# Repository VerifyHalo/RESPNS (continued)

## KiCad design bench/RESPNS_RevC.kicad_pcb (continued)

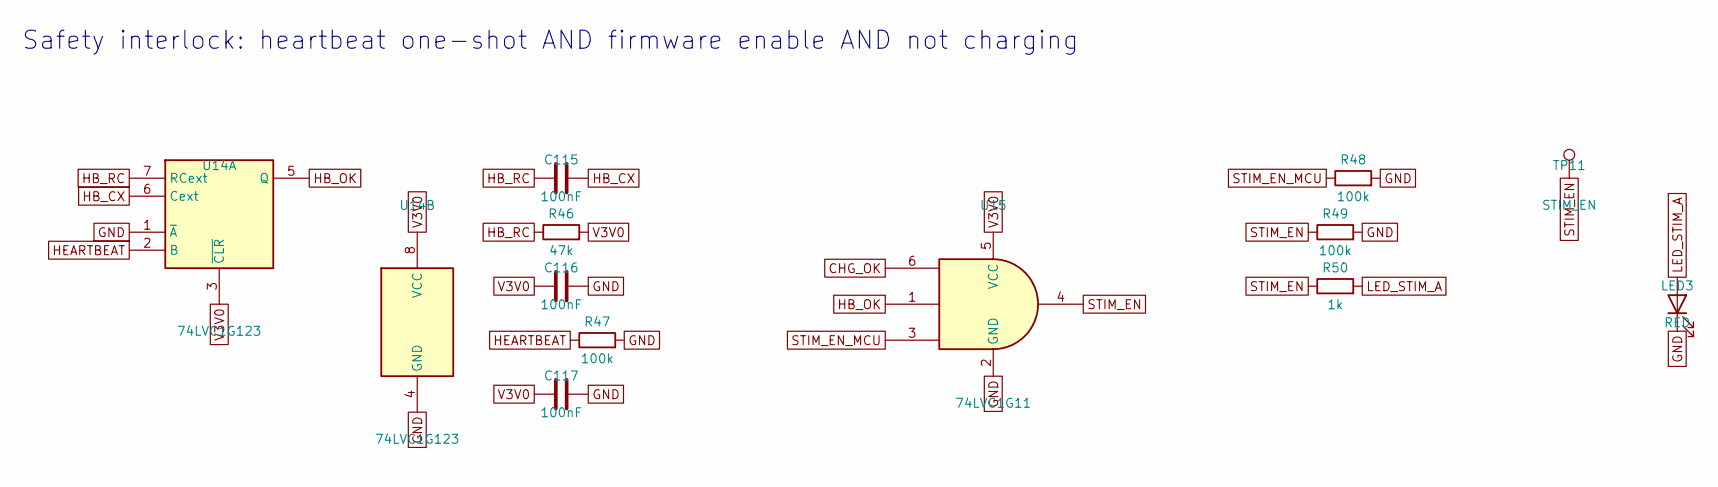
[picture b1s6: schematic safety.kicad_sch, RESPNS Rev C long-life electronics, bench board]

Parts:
C115, C116, C117: 100nF; C_0402_1005Metric; MPN CL05B104KO5NNNC
LED3: RED; LED_0603_1608Metric; MPN 19-217/R6C-AL1M2VY/6T
R46: 47k; R_0402_1005Metric; MPN 0402WGF4702TCE
R47, R48, R49: 100k; R_0402_1005Metric; MPN 0402WGF1003TCE
R50: 1k; R_0402_1005Metric; MPN 0402WGF1001TCE
TP11: STIM_EN; TestPoint_Pad_D1.0mm
U14: 74LVC1G123; VSSOP-8_2.3x2mm_P0.5mm; MPN SN74LVC1G123DCUR
U15: 74LVC1G11; SOT-363_SC-70-6; MPN SN74LVC1G11DCKR

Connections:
CHG_OK: U15.6; also elsewhere on the board
GND: C116.2, C117.2, LED3.1 (K), R47.2, R48.2, R49.2, U14.1 (~A), U14.4 (GND), U15.2 (GND); also elsewhere on the board
HB_CX: C115.2, U14.6 (Cext)
HB_OK: U14.5 (Q), U15.1
HB_RC: C115.1, R46.1, U14.7 (RCext)
HEARTBEAT: R47.1, U14.2 (B); also elsewhere on the board
LED_STIM_A: LED3.2 (A), R50.2
STIM_EN: R49.1, R50.1, TP11.1, U15.4; also elsewhere on the board
STIM_EN_MCU: R48.1, U15.3; also elsewhere on the board
V3V0: C116.1, C117.1, R46.2, U14.3 (~CLR), U14.8 (VCC), U15.5 (VCC); also elsewhere on the board

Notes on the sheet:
Safety interlock: heartbeat one-shot AND firmware enable AND not charging

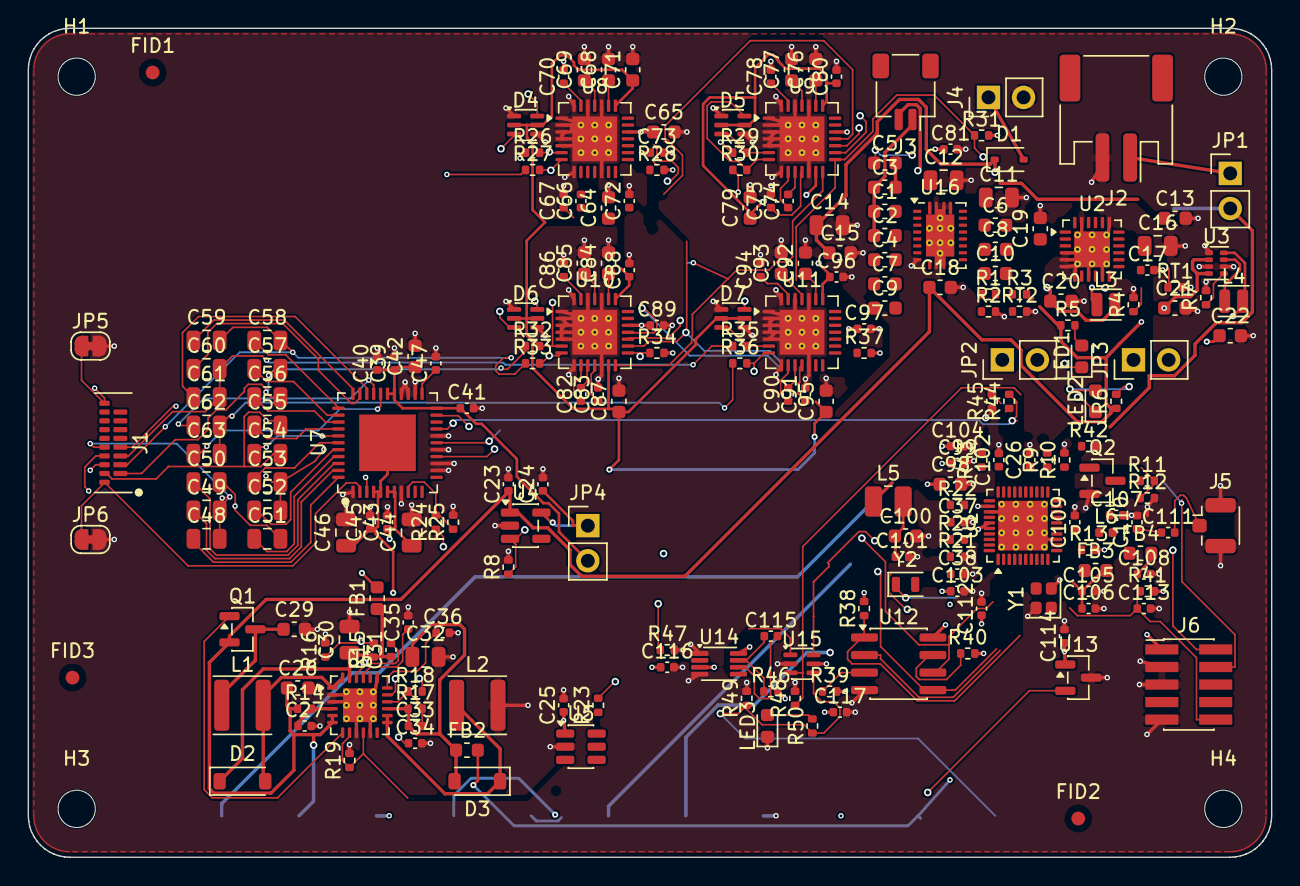
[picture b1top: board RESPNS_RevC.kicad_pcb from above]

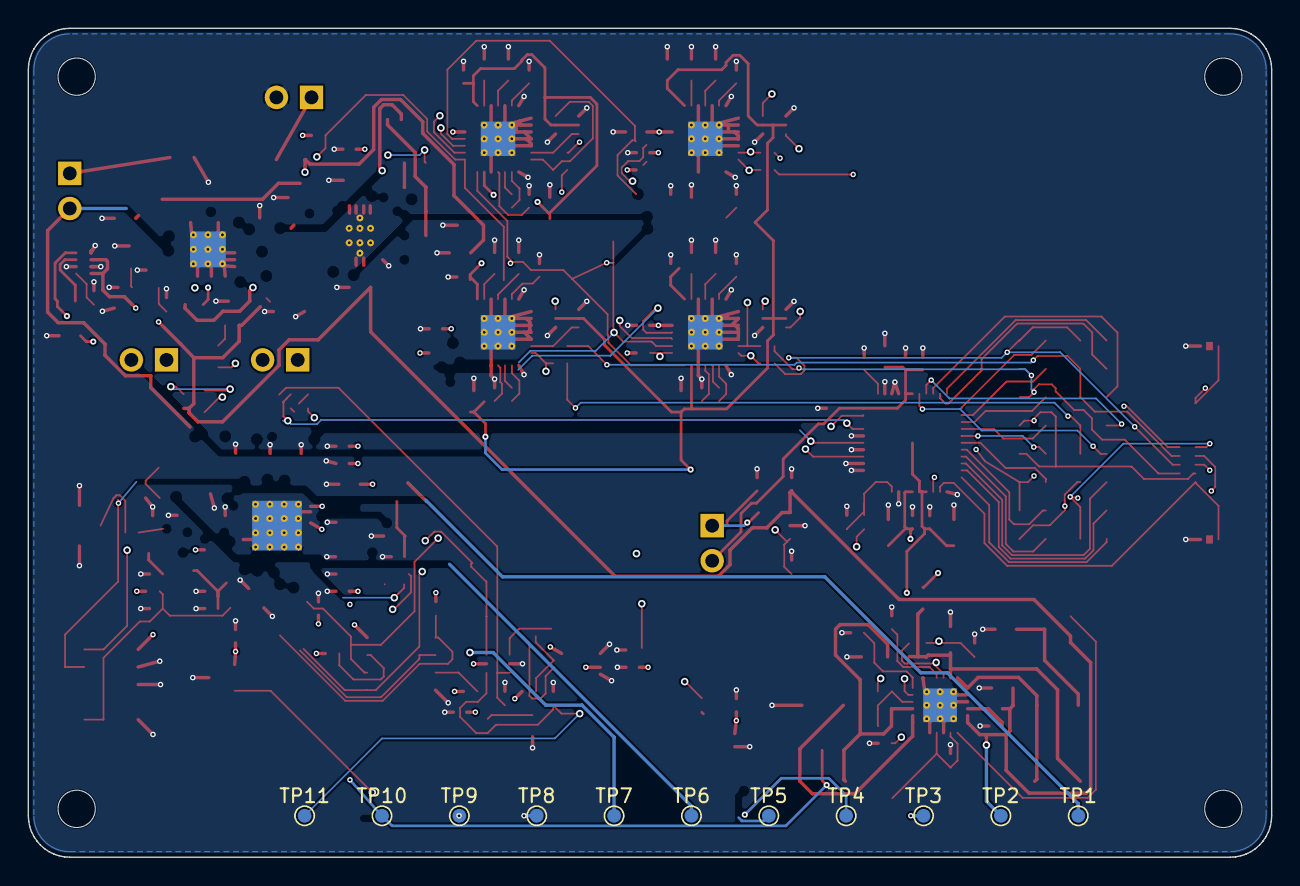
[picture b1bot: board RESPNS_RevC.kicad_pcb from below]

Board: 6 copper layers, 90.0 x 60.0 mm, 239 parts (11 on the bottom side), 159 nets.

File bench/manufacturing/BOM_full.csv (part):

Item,Qty,References,Value,Description,Manufacturer,MPN,Footprint,LCSC,JLC type,Unit price USD (qty10),Supply
1,1,J2,BATTERY,Li-ion cell (bench: protected 1S LiPo; implant: 200 mAh implant-grade cell),JST,S2B-PH-SM4-TB(LF)(SN),JST_PH_S2B-PH-SM4-TB_1x02-1MP_P2.00mm_Horizontal,C295747,Extended,0.2266,JLCPCB/LCSC
2,1,JP1,I_BAT,"Current-measurement header: fit a shorting jumper, or remove it and insert a uA meter (PPK2)",XFCN,PZ254V-11-02P,PinHeader_1x02_P2.54mm_Vertical,C492401,Extended,0.0184,JLCPCB/LCSC
3,1,J3,RX COIL,"Charging receiver coil (bench: Wurth 760308103205 Qi Rx coil, 11 uH; implant: 60-turn coil outside the can on a ferrite sheet)",JST,SM02B-SRSS-TB(LF)(SN),JST_SH_SM02B-SRSS-TB_1x02-1MP_P1.00mm_Horizontal,C160402,Extended,0.1335,JLCPCB/LCSC
4,1,C1,68nF,"68 nF 50 V X7R 0603, receiver series resonant capacitor",Samsung,CL10B683KB8NNNC,C_0603_1608Metric,C31658,Preferred extended,0.0189,JLCPCB/LCSC
5,1,C2,47nF,"47 nF 50 V X7R 0603, receiver series resonant capacitor",Samsung,CL10B473KB8NNNC,C_0603_1608Metric,C1622,Basic,0.0057,JLCPCB/LCSC
6,1,C3,39nF,"39 nF 50 V X7R 0603, receiver series resonant capacitor",Samsung,CL10B393KB8NNNC,C_0603_1608Metric,C318636,Extended,0.0068,JLCPCB/LCSC
7,1,C4,2.2nF,"2.2 nF 50 V C0G 0603, receiver parallel resonant capacitor",Samsung,CC0603JRNPO9BN222 (for CL10C222JB8NNNC),C_0603_1608Metric,C107043,Extended,0.0133,JLCPCB/LCSC
8,1,U16,BQ51013B,"Qi/WPC receiver, 5 V out; RILIM 4.9 kOhm: 54 mA nominal, 64 mA hard limit (RS-020 heat budget); zero drain when not charging",Texas Instruments,BQ51013BRHLR,Texas_VQFN-RHL-20_ThermalVias,C55663,Extended,3.4766,JLCPCB/LCSC
9,2,C5 C6,10nF,10 nF 50 V X7R 0603,Samsung,CL10B103KB8NNNC,C_0603_1608Metric,C1589,Extended,0.0071,JLCPCB/LCSC
10,2,C7 C8,470nF,470 nF 25 V X7R 0603,Samsung,CL10B474KA8NNNC,C_0603_1608Metric,C1623,Basic,0.0092,JLCPCB/LCSC
11,2,C9 C10,22nF,22 nF 50 V X7R 0603,Samsung,CL10B223KB8NNNC,C_0603_1608Metric,C21122,Basic,0.0057,JLCPCB/LCSC
12,7,C11 C12 C14 C30 C32 C44 C46,10uF,10 uF 25 V X5R 0805,Samsung,CL21A106KAYNNNE,C_0805_2012Metric,C15850,Basic,0.0312,JLCPCB/LCSC
13,2,C13 C15,100nF,100 nF 25 V X7R 0603,Samsung,CL10B104KA8NNNC,C_0603_1608Metric,C1590,Extended,0.0085,JLCPCB/LCSC
14,1,R1,4.7k,4.7k 1% 0402 resistor,UNI-ROYAL,0402WGF4701TCE,R_0402_1005Metric,C25900,Basic,0.0017,JLCPCB/LCSC
15,1,R2,196,196 1% 0402 resistor,UNI-ROYAL,CQ02WGF1960TCE (for 0402WGF1960TCE),R_0402_1005Metric,C966839,Extended,0.0011,JLCPCB/LCSC
16,1,R3,20k,20k 1% 0402 resistor,UNI-ROYAL,0402WGF2002TCE,R_0402_1005Metric,C25765,Basic,0.0010,JLCPCB/LCSC
17,2,RT1 RT2,10k NTC,10 kOhm NTC on the coil: receiver hardware over-temperature cut-off,Murata,NCP15XH103F03RC,R_0402_1005Metric,C77131,Extended,0.0166,JLCPCB/LCSC
18,1,J4,5V BENCH,Bench 5 V input instead of the coil,XFCN,PZ254V-11-02P,PinHeader_1x02_P2.54mm_Vertical,C492401,Extended,0.0184,JLCPCB/LCSC
19,1,D1,B5819WS,Schottky 1 A 40 V SOD-323,Changjiang,B5819WS,D_SOD-323,C22624,Extended,0.0258,JLCPCB/LCSC
20,1,U2,nPM1100,"Li-ion charger (36 mA, 4.1 V; RS-020 heat budget) + 3.0 V buck (VOUTBSET1/0 high), 800 nA battery drain",Nordic Semiconductor,NPM1100-QDAA-R7,QFN-24-1EP_4x4mm_P0.5mm_EP2.6x2.6mm_ThermalVias,C7249859,Extended,1.7006,JLCPCB/LCSC
21,1,C16,2.2uF,2.2 uF 25 V X5R 0805,Samsung,CL21A225KAFNNNE,C_0805_2012Metric,C87994,Extended,0.0419,JLCPCB/LCSC
22,14,C17 C23 C24 C25 C66 C70 C74 C78 C82 C86 C90 C94 C102 C103,1uF,1 uF 25 V X5R 0402,Samsung,CL05A105KA5NQNC,C_0402_1005Metric,C52923,Basic,0.0055,JLCPCB/LCSC
23,17,C18 C19 C20 C22 C28 C42 C64 C65 C68 C69 C76 C77 C84 C85 C92 C93 C98,10uF,10 uF 10 V X5R 0603,Samsung,CL10A106KP8NNNC,C_0603_1608Metric,C19702,Basic,0.0168,JLCPCB/LCSC
24,2,L3 L4,2.2uH,2.2 uH 2016 power inductor (nPM1100 buck),Changjiang,FTC201608S2R2MBCA (for FTC201607S2R2MBCA),L_Changjiang_FTC201607S,C5832332,Extended,0.0978,JLCPCB/LCSC
25,2,R4 R7,15.8k,15.8k 1% 0402 resistor,UNI-ROYAL,0402WGF1582TCE,R_0402_1005Metric,C26956,Extended,0.0012,JLCPCB/LCSC
26,5,R5 R6 R24 R45 R50,1k,1k 1% 0402 resistor,UNI-ROYAL,0402WGF1001TCE,R_0402_1005Metric,C11702,Basic,0.0013,JLCPCB/LCSC
27,1,LED1,ORANGE,ORANGE LED 0603,Everlight,19-217/S2C-AL1M2VY/6T,LED_0603_1608Metric,C2987557,Extended,0.0295,JLCPCB/LCSC
28,2,LED2 LED3,RED,RED LED 0603,Everlight,19-217/R6C-AL1M2VY/6T,LED_0603_1608Metric,C2986060,Extended,0.0149,JLCPCB/LCSC
29,1,JP2,I_SYS,"Current-measurement header: fit a shorting jumper, or remove it and insert a uA meter (PPK2)",XFCN,PZ254V-11-02P,PinHeader_1x02_P2.54mm_Vertical,C492401,Extended,0.0184,JLCPCB/LCSC
30,1,U3,TPS62841,"1.2 V buck for the MAX30003 cores, 60 nA Iq",Texas Instruments,TPS62841DLCR,VSON-8_1.5x2mm_P0.5mm,C2860681,Extended,1.8625,JLCPCB/LCSC
31,7,C21 C29 C71 C79 C87 C95 C100,4.7uF,4.7 uF 16 V X5R 0603,Samsung,CL10A475KO8NNNC,C_0603_1608Metric,C19666,Basic,0.0150,JLCPCB/LCSC
32,1,JP3,I_AFE,"Current-measurement header: fit a shorting jumper, or remove it and insert a uA meter (PPK2)",XFCN,PZ254V-11-02P,PinHeader_1x02_P2.54mm_Vertical,C492401,Extended,0.0184,JLCPCB/LCSC
33,1,U4,TPS7A0233,"3.3 V 25 nA-Iq LDO for the RHS2116, enabled by firmware only after both stimulator rails are verified",Texas Instruments,TPS7A0233PDBVR,SOT-23-5,C2887324,Extended,0.9734,JLCPCB/LCSC
34,18,R8 R12 R13 R19 R20 R22 R25 R28 R31 R34 R37 R38 R39 R40 R41 R47 R48 R49,100k,100k 1% 0402 resistor,UNI-ROYAL,0402WGF1003TCE,R_0402_1005Metric,C25741,Basic,0.0009,JLCPCB/LCSC
35,1,JP4,I_RHS,"Current-measurement header: fit a shorting jumper, or remove it and insert a uA meter (PPK2)",XFCN,PZ254V-11-02P,PinHeader_1x02_P2.54mm_Vertical,C492401,Extended,0.0184,JLCPCB/LCSC
36,1,U5,TPS22917,Load switch for the rail-sense offset divider (10 nA off),Texas Instruments,TPS22917DBVR,SOT-23-6,C2681320,Extended,0.3734,JLCPCB/LCSC
37,2,R9 R10,10M,10M 1% 0402 resistor,UNI-ROYAL,0402WGF1005TCE,R_0402_1005Metric,C26082,Preferred extended,0.0012,JLCPCB/LCSC
38,27,C26 C27 C37 C38 C39 C40 C41 C43 C45 C72 C73 C80 C81 C88 C89 C96 C97 C99 C101 C105 C107 C112 C113 C114 C115 C116 C117,100nF,100 nF 16 V X7R 0402,Samsung,CL05B104KO5NNNC,C_0402_1005Metric,C1525,Basic,0.0024,JLCPCB/LCSC
39,1,R11,10k,10k 1% 0402 resistor,UNI-ROYAL,0402WGF1002TCE,R_0402_1005Metric,C25744,Basic,0.0015,JLCPCB/LCSC
40,1,Q2,2N7002,Charger present: pulls CHG_OK low and disables stimulation in hardware,Changjiang,2N7002,SOT-23,C8545,Basic,0.0159,JLCPCB/LCSC
41,1,U6,TPS65131,"+/-6.5 V stimulator supply, enabled only during therapies",Texas Instruments,TPS65131RGER,VQFN-24-1EP_4x4mm_P0.5mm_EP2.45x2.45mm_ThermalVias,C87663,Extended,2.96,JLCPCB/LCSC
42,1,R14,100,100 1% 0402 resistor,UNI-ROYAL,0402WGF1000TCE,R_0402_1005Metric,C25076,Basic,0.0012,JLCPCB/LCSC
43,1,Q1,AO3401A,"P-MOSFET, boost input disconnect (TPS65131 BSW): zero current when off",AOS,AO3401A,SOT-23,C15127,Basic,0.0814,JLCPCB/LCSC
44,2,L1 L2,4.7uH,4.7 uH 1.5 A power inductor,Sunlord,SWPA4020S4R7MT,L_Sunlord_SWPA4020S,C48427,Extended,0.0623,JLCPCB/LCSC
45,2,D2 D3,B5819W,Schottky 1 A 40 V,Changjiang,B5819W,D_SOD-123,C8598,Basic,0.0256,JLCPCB/LCSC
46,1,R15,562k,562k 1% 0402 resistor,UNI-ROYAL,CQ02WGF5623TCE,R_0402_1005Metric,C966760,Extended,0.002,JLCPCB/LCSC
47,1,R16,130k,130k 1% 0402 resistor,UNI-ROYAL,0402WGF1303TCE,R_0402_1005Metric,C52929,Extended,0.0013,JLCPCB/LCSC
48,3,C31 C33 C111,18pF,18 pF 50 V C0G 0402,Samsung,CL05C180JB5NNNC,C_0402_1005Metric,C307443,Extended,0.01,JLCPCB/LCSC
49,1,R17,649k,649k 1% 0402 resistor,UNI-ROYAL,0402WGF6493TCE,R_0402_1005Metric,C423143,Extended,0.001,JLCPCB/LCSC
50,1,R18,121k,121k 1% 0402 resistor,UNI-ROYAL,0402WGF1213TCE,R_0402_1005Metric,C11693,Extended,0.0010,JLCPCB/LCSC
51,1,C34,220nF,220 nF 25 V X5R 0402,Samsung,CL05A224KA5NNNC,C_0402_1005Metric,C47129,Extended,0.0073,JLCPCB/LCSC
52,3,C35 C47 C104,10nF,10 nF 50 V X7R 0402,Samsung,CL05B103KB5NNNC,C_0402_1005Metric,C15195,Basic,0.0038,JLCPCB/LCSC
53,1,C36,4.7nF,4.7 nF 50 V X7R 0402,Samsung,CL05B472KB5NNNC,C_0402_1005Metric,C84705,Extended,0.0044,JLCPCB/LCSC
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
